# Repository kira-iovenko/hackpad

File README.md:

# Kira Hackpad

A 12-key custom macropad with a rotary encoder and a little OLED screen, built from scratch - PCB, case, and firmware.

## Features

- 12 keys in a 4x3 grid
- Rotary encoder for volume
- 0.91" OLED display for status
- Runs on a Seeed XIAO RP2040
- QMK firmware

## Hardware

- Controller: Seeed XIAO RP2040
- Switches: 12x Cherry MX
- Diodes: 12x 1N4148
- Encoder: EC11 rotary encoder
- Display: 0.91" SSD1306 OLED (128x32)

## PCB

Designed in KiCad. It's a simple 2-layer board - a 2x4 switch matrix with per-key diodes, XIOA footprint, encoder, and OLED. Source files are in ['pcb/'](pcb/) (schematic, layout, and STEP export).

## Case

Designed in Fusion 360, in three printed parts: the angle, the base where the PCB sits, and the top cover. They fits together using 5 M3 bolts and heatset inserts - 4 cor the case and one for the PCB. The design is in ['cad/'](cad/).

## Firmware

Written with QMK and lives in ['firmware/'](firmware/). The keys are laid out for editing + media shortcuts, the encoder controls volume, and OLED shows a status readout. A ready-to-flash `firmware.uf2` is in ['production/'](production/).

### Keymap

| | | |
|-|-|-|
| Undo | Redo  | Cut  | Prev |
| Copy | Paste | Save | Play |
| All  | Find  | Mute | Next |

Encoder: turn = Volume Down / Up

"Undo", "Redo", "Cut", "Prev", "Copy", "Paste", "Save", "Play", "Select All", and "Find" are sent as **Ctrl+key**, which works on Windows. On macOS remap them to `G(...)` (Cmd) in `keymaps/default/keymap.c`.

### Flash

To flash: put the XIAO RP2040 into bootloader mode (double-tap RESET or hold BOOT while plugging in). It appears as a USB drive - copy `firmware.utf2` onto it. The board reboots into the firmware.

### Customizing

- Keys - edit the `LAYOUT(...)` block in `keymaps/default/keymap.c`.
- Encoder - edit the `encoder_map` in the same file.
- OLED text - edit `oled_task_user()` in the same file.

## Built with

- KiCad (PCB)
- Fusion 360 (case)
- QMK (firmware)

## BOM (Bill of Materials)

## Bill of Materials

The complete itemized parts list is in **[`BOM.csv`](BOM.csv)**.

Prices are indicative per-unit estimates or previously observed listings, not verified live checkout prices. Shipping, tax, supplier pack sizes, PCB manufacturing minimums, and 3D-printing quotes are excluded.

| Component | Qty | Unit price (USD) | Extended cost (USD) | Purchase/source |
|---|---:|---:|---:|---|
| Seeed Studio XIAO RP2040 | 1 | $3.99 | $3.99 | [Link](https://www.seeedstudio.com/XIAO-RP2040-v1-0-p-5026.html) |
| 0.91 inch SSD1306 OLED display 128x32 I2C | 1 | $3.73 | $3.73 | [Link](https://www.robotshop.com/products/091-inch-128x32-i2c-oled-display-blue) |
| EC11 rotary encoder | 1 | $1.50 | $1.50 | [Link](https://www.aliexpress.com/w/wholesale-ec11-rotary-encoder.html) |
| MX-style mechanical switches | 12 | $0.40 | $4.80 | [Link](https://www.aliexpress.com/w/wholesale-mx-mechanical-switch.html) |
| Blank DSA keycaps white | 12 | $0.60 | $7.20 | [Link](https://www.aliexpress.com/w/wholesale-blank-dsa-keycaps.html) |
| M3 x 16 mm screws | 4 | $0.15 | $0.60 | [Link](https://www.mcmaster.com/products/socket-head-screws/thread-size~m3/) |
| M3 x 12 mm screw | 1 | $0.15 | $0.15 | [Link](https://www.mcmaster.com/products/socket-head-screws/thread-size~m3/) |
| M3 x 5 x 4 mm heat-set inserts | 5 | $0.25 | $1.25 | [Link](https://www.aliexpress.com/w/wholesale-m3-heat-set-insert.html) |
| 1N4148 through-hole diodes | 12 | $0.10 | $1.20 | [Link](https://www.digikey.com/en/products/result?keywords=1N4148) |
| 3D-printed case (3 parts) | 1 | $3.00 | $3.00 | [CAD files](cad/) |
| Custom hackpad PCB | 1 | $2.00 | $2.00 | [Link](https://jlcpcb.com/) |
| **Estimated total** | | | **$29.42** | |

**Pricing note:** Several links lead to product searches, not exact purchasable variants. The PCB $2.00 and printed case $3.00 are allowances, not supplier quotes.

### Hack Club Grants

I used/received the following Hack Club grants during the project:

* **Hackpad Kit!** - Hackpad kit containing parts for the project
* **Printing Legion Grant** - $8 shipping credit for a part under 300g
* **Soldering Iron Grant** - $18 grant toward a soldering iron
* **Hackpad PCB Grant** - $10 JLCPCB credit for the Hackpad PCB

## Inspiration

It was was created using guide from Hack Club's Stardance program as a starting point. It was also inspired by [Orpheuspad](https://github.com/qcoral/orpheuspad) and the wider custom hackpad community. Thanks for sharing your bilds!

## Author

Made with ❤️ by [@kira-iovenko](https://github.com/kira-iovenko)

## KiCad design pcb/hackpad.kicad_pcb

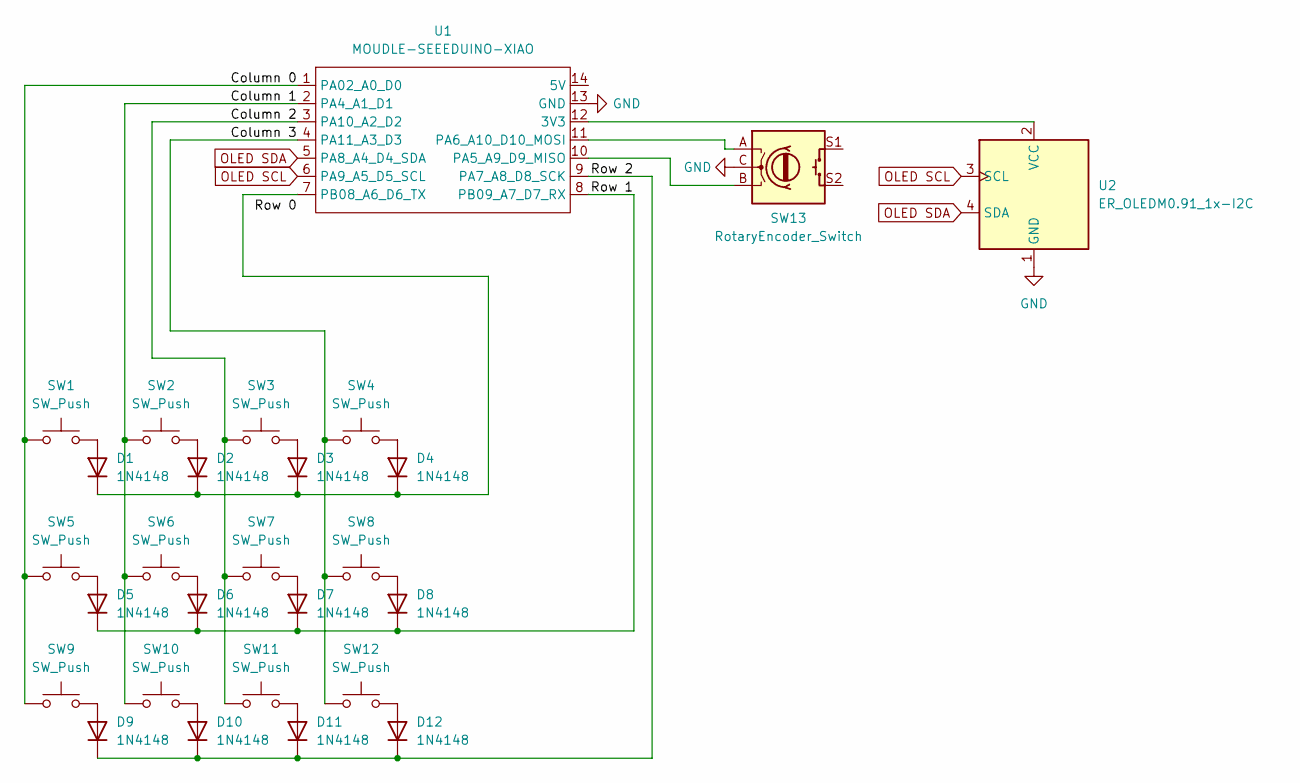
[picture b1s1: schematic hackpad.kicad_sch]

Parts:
D1, D2, D3, D4, D5, D6, D7, D8, D9, D10, D11, D12: 1N4148; D_DO-35_SOD27_P7.62mm_Horizontal
SW1, SW2, SW3, SW4, SW5, SW6, SW7, SW8, SW9, SW10, SW11, SW12: SW_Push; SW_Cherry_MX_1.00u_PCB
SW13: RotaryEncoder_Switch; RotaryEncoder_Alps_EC11E-Switch_Vertical_H20mm
U1: MOUDLE-SEEEDUINO-XIAO; XIAO-Generic-Hybrid-14P-2.54-21X17.8MM
U2: ER_OLEDM0.91_1x-I2C

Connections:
/Column 0: SW1.1, SW5.1, SW9.1, U1.1 (PA02_A0_D0)
/Column 1: SW2.1, SW6.1, SW10.1, U1.2 (PA4_A1_D1)
/Column 2: SW3.1, SW7.1, SW11.1, U1.3 (PA10_A2_D2)
/Column 3: SW4.1, SW8.1, SW12.1, U1.4 (PA11_A3_D3)
/Row 1: D5.1 (K), D6.1 (K), D7.1 (K), D8.1 (K), U1.8 (PB09_A7_D7_RX)
/Row 2: D9.1 (K), D10.1 (K), D11.1 (K), D12.1 (K), U1.9 (PA7_A8_D8_SCK)
GND: SW13.C, U1.13 (GND), U2.1 (GND)
unnamed: D1.2 (A), SW1.2
unnamed: D1.1 (K), D2.1 (K), D3.1 (K), D4.1 (K), U1.7 (PB08_A6_D6_TX)
unnamed: D2.2 (A), SW2.2
unnamed: D3.2 (A), SW3.2
unnamed: D4.2 (A), SW4.2
unnamed: D5.2 (A), SW5.2
unnamed: D6.2 (A), SW6.2
unnamed: D7.2 (A), SW7.2
unnamed: D8.2 (A), SW8.2
unnamed: D9.2 (A), SW9.2
unnamed: D10.2 (A), SW10.2
unnamed: D11.2 (A), SW11.2
unnamed: D12.2 (A), SW12.2
unnamed: U1.12 (3V3), U2.2 (VCC)
unnamed: SW13.B, U1.10 (PA5_A9_D9_MISO)
unnamed: SW13.A, U1.11 (PA6_A10_D10_MOSI)
OLED SCL: U1.6 (PA9_A5_D5_SCL), U2.3 (SCL)
OLED SDA: U1.5 (PA8_A4_D4_SDA), U2.4 (SDA)

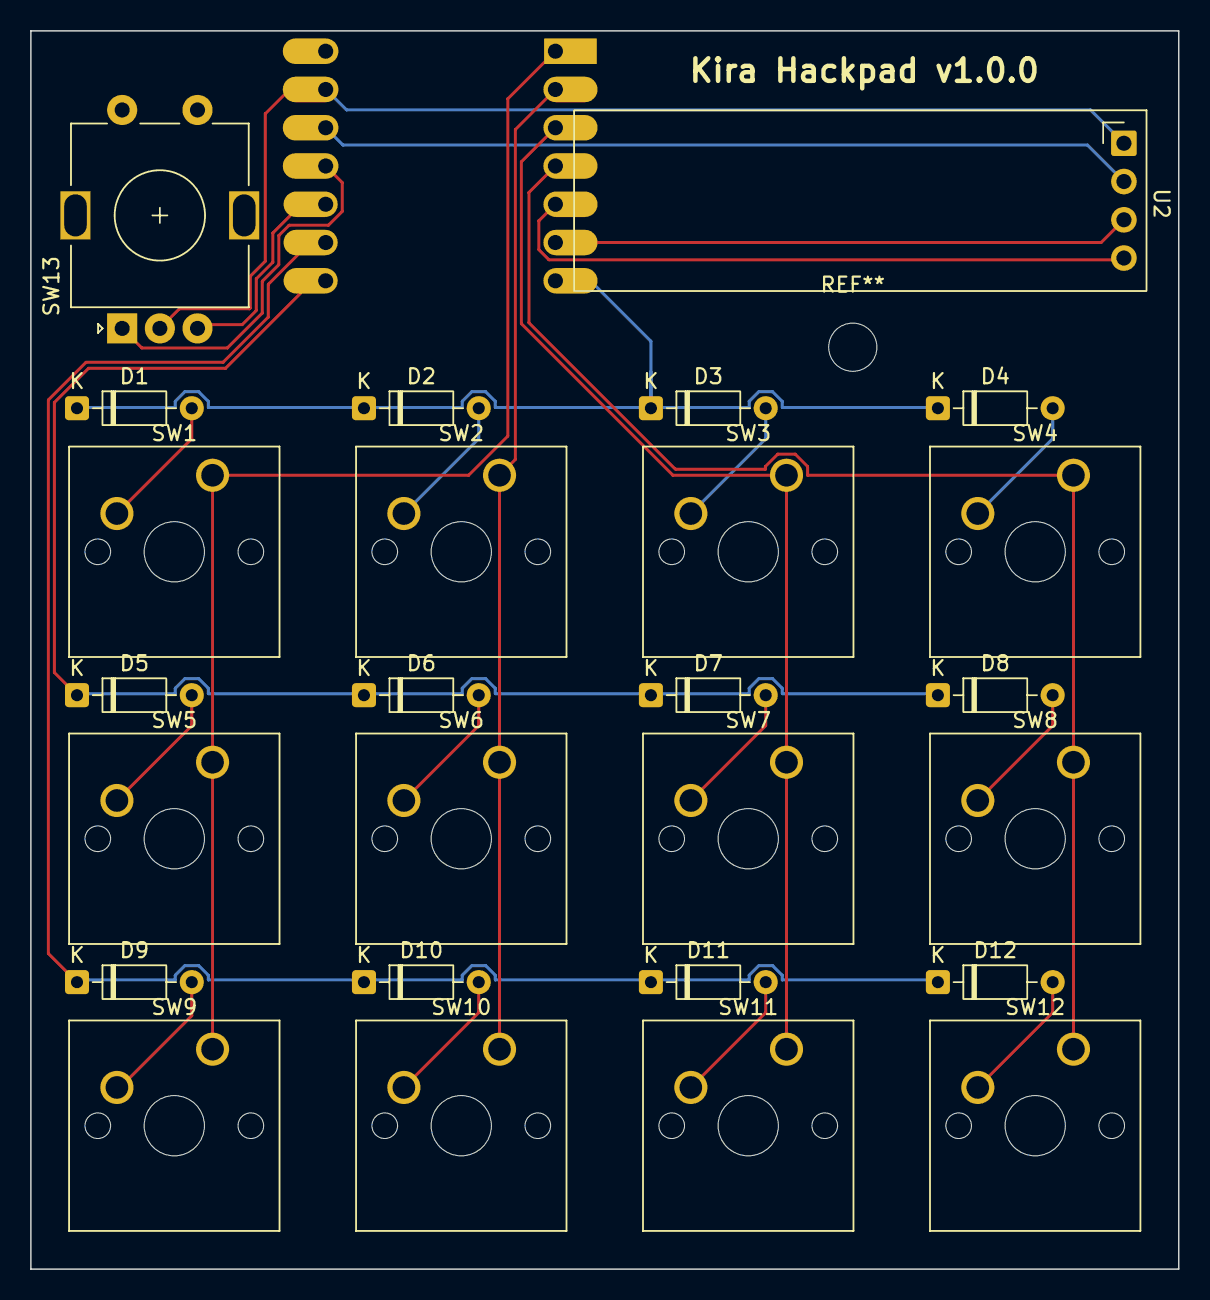
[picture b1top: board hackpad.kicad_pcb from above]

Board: 2 copper layers, 76.2 x 82.2 mm, 27 parts (1 on the bottom side), 25 nets.
